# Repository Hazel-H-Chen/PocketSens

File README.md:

# PocketSens Portable Sensor Suite

PocketSens is a portable environmental sensor platform designed to measure environmental and physical data beyond the capabilities of a typical smartphone. The system integrates multiple sensors on a custom four layer PCB and provides real time measurements through a small OLED display and rotary encoder interface.

## Overview

PocketSens is built around an ARM Cortex M0+ SAMD21 microcontroller and communicates with several sensors over an I²C bus. The device collects environmental measurements and displays them directly on the device, allowing users to monitor conditions in real time.

The system is designed as a compact handheld tool capable of measuring atmospheric and environmental parameters in a single portable device. 

## Sensors

The device integrates several sensors including:

* BME680 environmental sensor
  gas, humidity, pressure, temperature
* BMP390 barometric pressure sensor
* MLX90614 infrared temperature sensor
* AS3935 lightning detection sensor

Together these sensors allow the device to measure a wide range of environmental conditions in real time. 

## Hardware

* Custom four layer PCB designed in KiCad
* ARM Cortex M0+ SAMD21 microcontroller
* OLED display for live data output
* Rotary encoder for user interface
* I²C sensor bus architecture

## Features

* Multi sensor environmental monitoring
* Real time data display on OLED screen
* Lightning detection capability
* Infrared temperature sensing
* Compact portable design

## Repository Contents

pcb/
KiCad schematic and PCB layout files

images/
Board photos and layout screenshots

docs/
Additional design notes and documentation

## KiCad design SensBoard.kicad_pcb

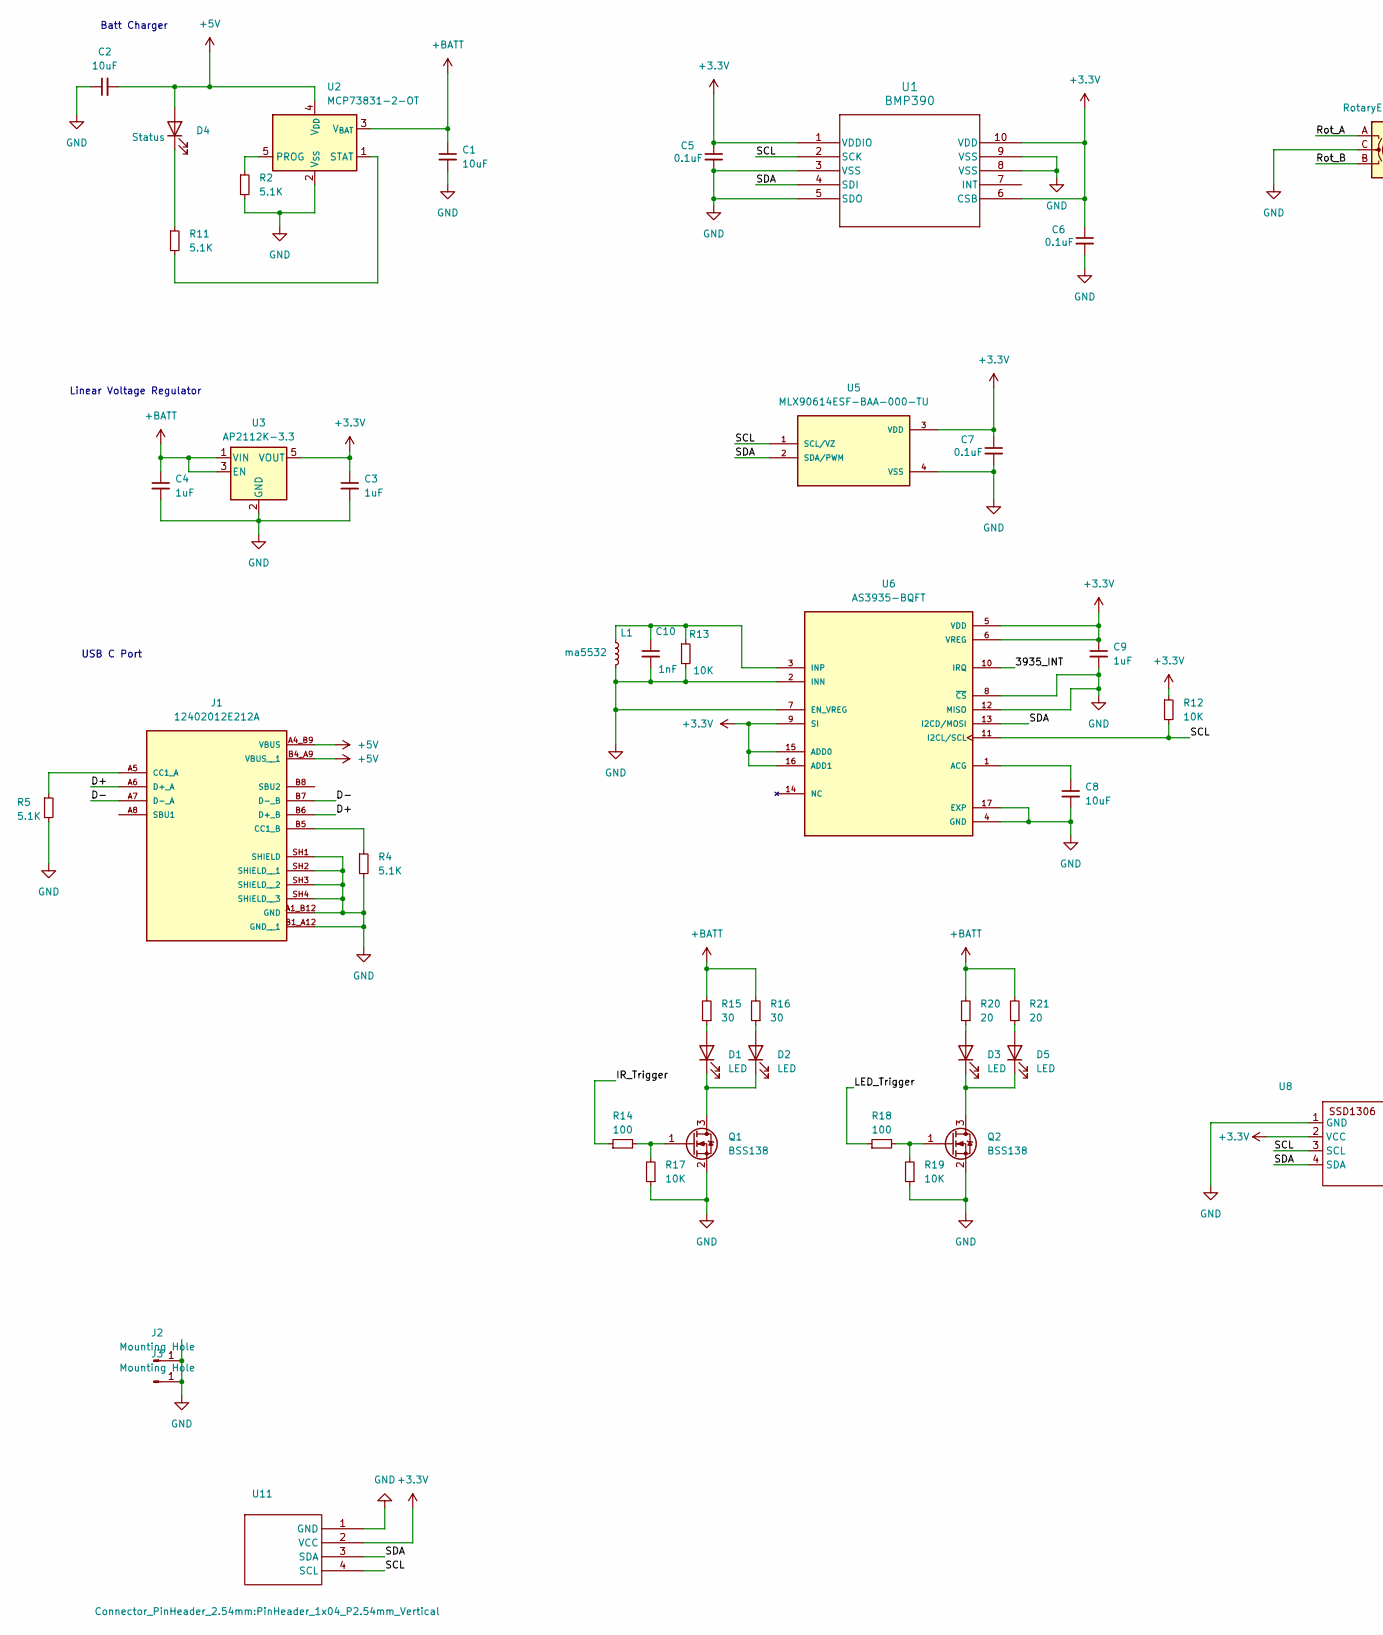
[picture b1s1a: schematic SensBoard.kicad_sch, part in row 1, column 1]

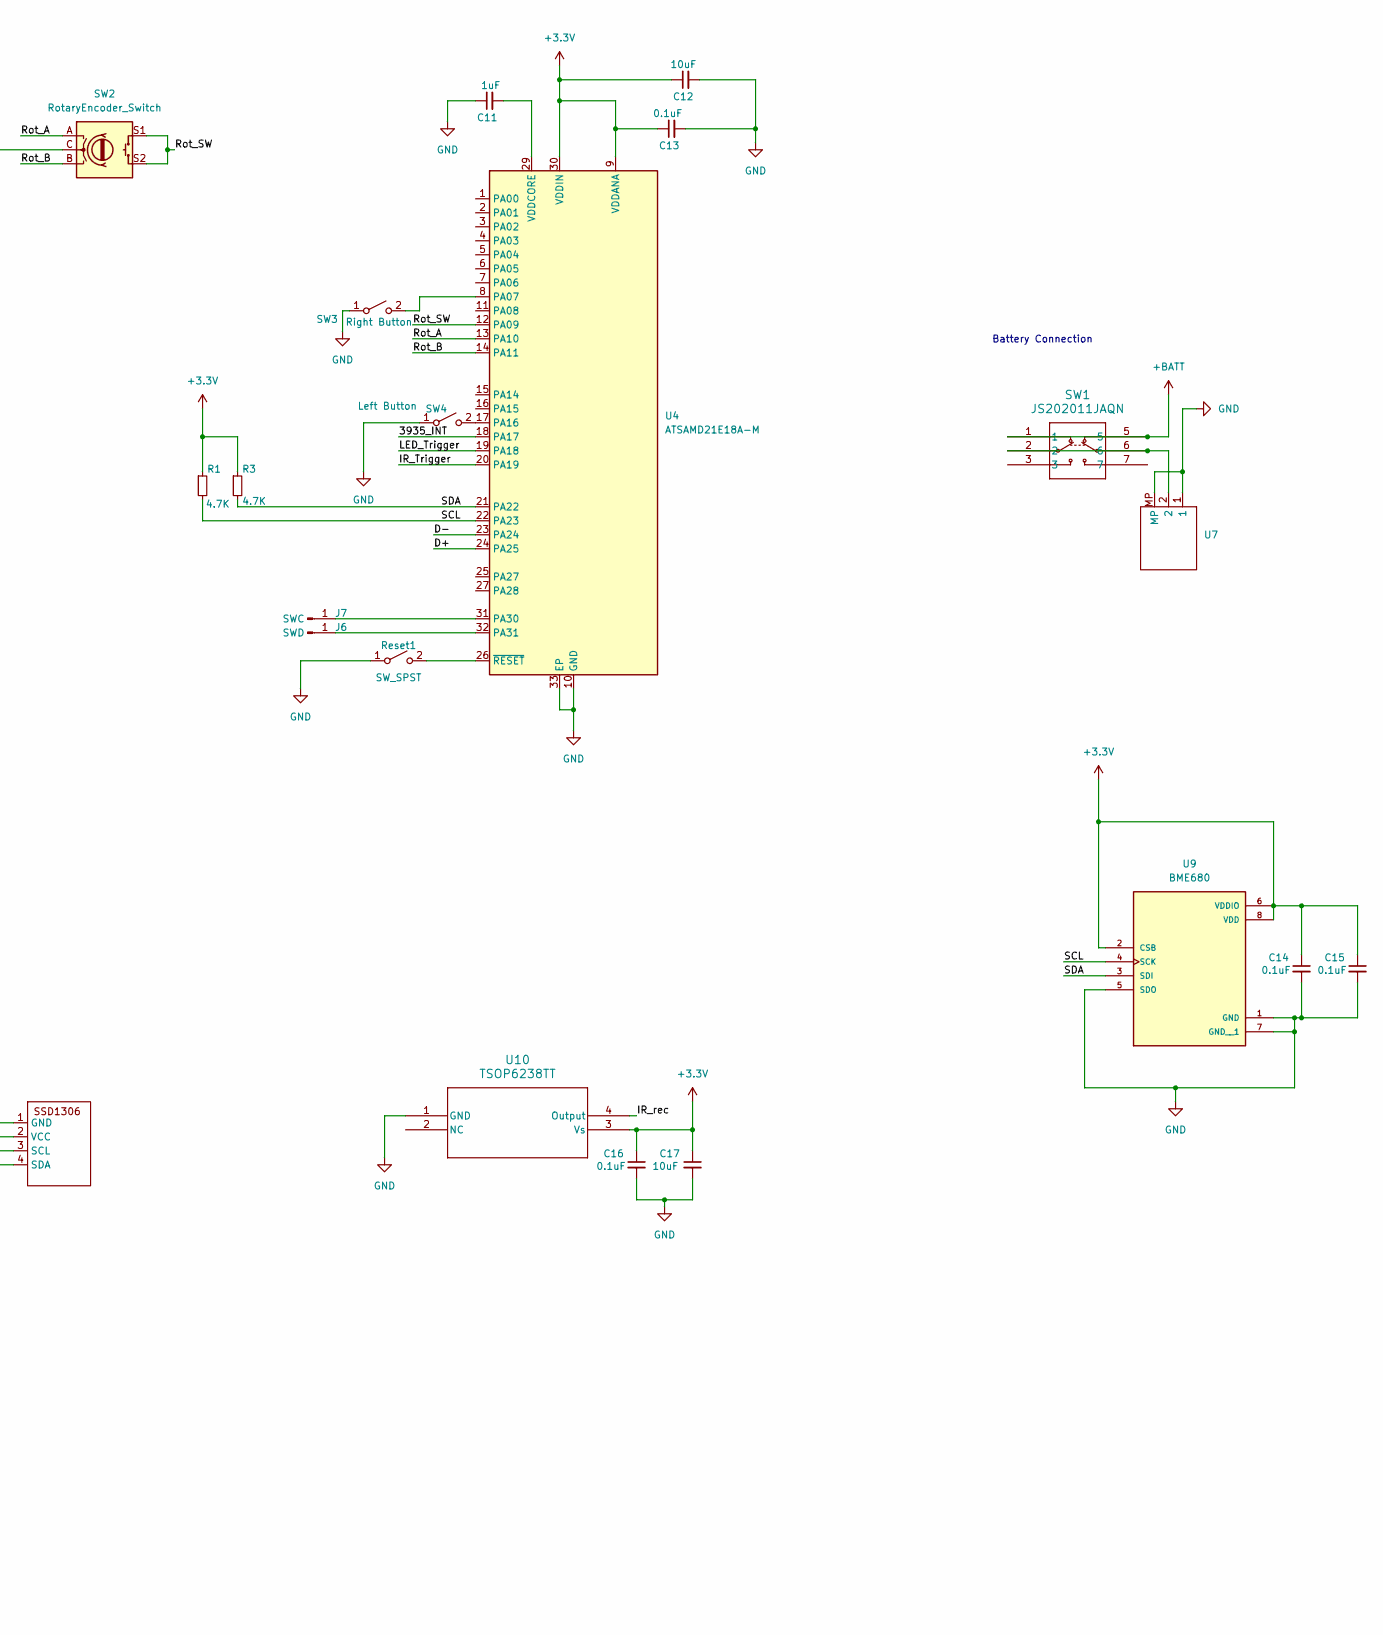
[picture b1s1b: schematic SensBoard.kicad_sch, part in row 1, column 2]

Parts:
C1, C2, C8, C12, C17: 10uF; C_0603_1608Metric
C3, C4, C9, C11: 1uF; C_0603_1608Metric
C5, C6, C7, C13, C14, C15, C16: 0.1uF; C_0603_1608Metric
C10: 1nF; C_0603_1608Metric
D1, D2, D3, D5: LED; LED_PLCC_2835
D4: Status; LED_0603_1608Metric
J1: 12402012E212A; AMPHENOL_12402012E212A; PARTREV 4
J2, J3: Mounting Hole; MountingHole_2.2mm_M2_DIN965_Pad
J6: SWD; PinHeader_1x01_P2.54mm_Vertical
J7: SWC; PinHeader_1x01_P2.54mm_Vertical
L1: ma5532; MA5532-AE
Q1, Q2: BSS138; SOT-23
R1, R3: 4.7K; R_0603_1608Metric
R2, R11: 5.1K; R_0402_1005Metric
R4, R5: 5.1K; R_0603_1608Metric
R12: 10K; R_0402_1005Metric_Pad0.72x0.64mm_HandSolder
R13, R17, R19: 10K; R_0603_1608Metric
R14, R18: 100; R_0603_1608Metric
R15, R16: 30; R_2512_6332Metric
R20, R21: 20; R_0603_1608Metric
Reset1: SW_SPST; SolderJumper-2_P1.3mm_Open_TrianglePad1.0x1.5mm
SW1: JS202011JAQN; JS202011JAQN_CNK
SW2: RotaryEncoder_Switch; RotaryEncoder_Alps_EC11E-Switch_Vertical_H20mm
SW3: Right Button; SW2_KSS341GLFS_CNK
SW4: Left Button; SW2_KSS341GLFS_CNK
U1: BMP390; 10LGA_2X2X0p75_BOS
U2: MCP73831-2-OT; SOT-23-5
U3: AP2112K-3.3; SOT-23-5
U4: ATSAMD21E18A-M; QFN-32-1EP_5x5mm_P0.5mm_EP3.6x3.6mm
U5: MLX90614ESF-BAA-000-TU; TO254P942H425-4; PARTREV 13
U6: AS3935-BQFT; QFN65P400X400X80-17N
U7: JST_PH_S2B-PH-SM4-TB_1x02-1MP_P2.00mm_Horizontal
U8: 128x64OLED
U9: BME680; PSON80P300X300X100-8N; PARTREV 1.9
U10: TSOP6238TT; SOJ_6238TT_VIS-M
U11: PinHeader_1x04_P2.54mm_Vertical

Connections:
+3.3V: C3.1, C5.1, C6.1, C7.1, C9.1, C12.1, C13.1, C14.1, C15.1, C16.1, C17.1, R1.1, R3.1, R12.1, U1.1 (VDDIO), U1.6 (CSB), U1.10 (VDD), U3.5 (VOUT), U4.9 (VDDANA), U4.30 (VDDIN), U5.3 (VDD), U6.5 (VDD), U6.6 (VREG), U6.9 (SI), U6.15 (ADD0), U6.16 (ADD1), U8.2 (VCC), U9.2 (CSB), U9.6 (VDDIO), U9.8 (VDD), U10.3 (Vs), U11.2 (VCC)
+5V: C2.2, D4.2 (A), J1.A4_B9 (VBUS), J1.B4_A9 (VBUS__1), U2.4 (V_{DD})
+BATT: C1.1, C4.1, R15.2, R16.2, R20.2, R21.2, SW1.1, SW1.5, U2.3 (V_{BAT}), U3.1 (VIN), U3.3 (EN)
/3935_INT: U4.18 (PA17), U6.10 (IRQ)
/D+: J1.A6 (D+_A), J1.B6 (D+_B), U4.24 (PA25)
/D-: J1.A7 (D-_A), J1.B7 (D-_B), U4.23 (PA24)
/IR_Trigger: R14.1, U4.20 (PA19)
/IR_rec: U10.4 (Output)
/LED_Trigger: R18.1, U4.19 (PA18)
/Rot_A: SW2.A, U4.13 (PA10)
/Rot_B: SW2.B, U4.14 (PA11)
/Rot_SW: SW2.S1, SW2.S2, U4.12 (PA09)
/SCL: R1.2, R12.2, U1.2 (SCK), U4.22 (PA23), U5.1 (SCL/VZ), U6.11 (I2CL/SCL), U8.3 (SCL), U9.4 (SCK), U11.4 (SCL)
/SDA: R3.2, U1.4 (SDI), U4.21 (PA22), U5.2 (SDA/PWM), U6.13 (I2CD/MOSI), U8.4 (SDA), U9.3 (SDI), U11.3 (SDA)
GND: C1.2, C2.1, C3.2, C4.2, C5.2, C6.2, C7.2, C8.2, C9.2, C10.2, C11.1, C12.2, C13.2, C14.2, C15.2, C16.2, C17.2, J1.A1_B12 (GND), J1.B1_A12 (GND__1), J1.SH1 (SHIELD), J1.SH2 (SHIELD__1), J1.SH3 (SHIELD__2), J1.SH4 (SHIELD__3), J2.1, J3.1, L1.2, Q1.2 (S), Q2.2 (S), R2.2, R4.2, R5.2, R13.2, R17.1, R19.1, Reset1.1 (A), SW2.C, SW3.1 (A), SW4.1 (A), U1.3 (VSS), U1.5 (SDO), U1.8 (VSS), U1.9 (VSS), U2.2 (V_{SS}), U3.2 (GND), U4.10 (GND), U4.28 (GND), U4.33 (EP), U5.4 (VSS), U6.2 (INN), U6.4 (GND), U6.7 (EN_VREG), U6.8 (~CS), U6.12 (MISO), U6.17 (EXP), U7.1, U7.MP, U8.1 (GND), U9.1 (GND), U9.5 (SDO), U9.7 (GND__1), U10.1 (GND), U11.1 (GND)
unnamed: D1.2 (A), R15.1
unnamed: D1.1 (K), D2.1 (K), Q1.3 (D)
unnamed: D2.2 (A), R16.1
unnamed: D3.2 (A), R20.1
unnamed: D3.1 (K), D5.1 (K), Q2.3 (D)
unnamed: D4.1 (K), R11.1
unnamed: D5.2 (A), R21.1
unnamed: J1.A5 (CC1_A), R5.1
unnamed: J1.B5 (CC1_B), R4.1
unnamed: J6.1, U4.32 (PA31)
unnamed: J7.1, U4.31 (PA30)
unnamed: Q1.1 (G), R14.2, R17.2
unnamed: Q2.1 (G), R18.2, R19.2
unnamed: Reset1.2 (B), U4.26 (~RESET)
unnamed: SW1.2, SW1.6, U7.2
unnamed: SW3.2 (B), U4.8 (PA07)
unnamed: SW4.2 (B), U4.17 (PA16)
unnamed: R2.1, U2.5 (PROG)
unnamed: R11.2, U2.1 (STAT)
unnamed: C11.2, U4.29 (VDDCORE)
unnamed: C8.1, U6.1 (ACG)
unnamed: C10.1, L1.1, R13.1, U6.3 (INP)

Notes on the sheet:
Batt Charger
Linear Voltage Regulator
USB C Port
Battery Connection

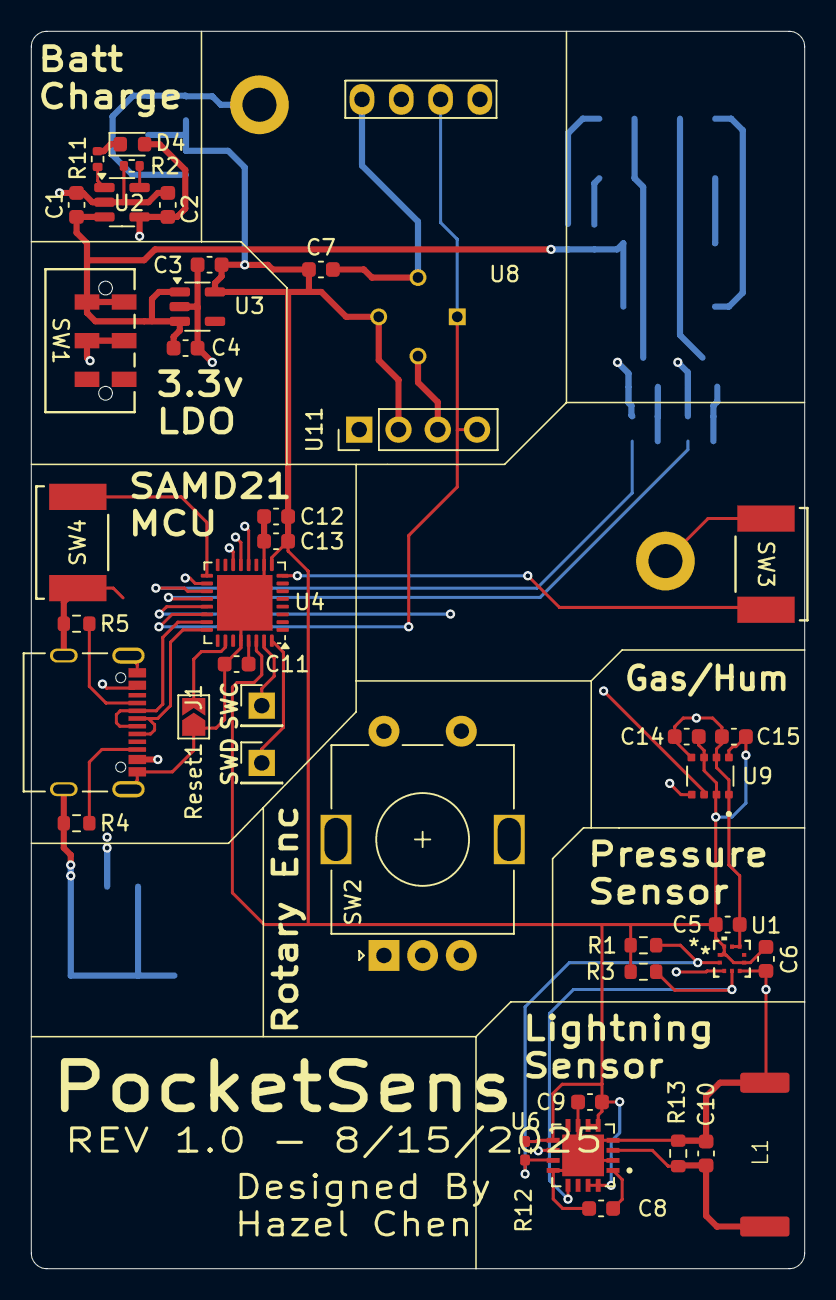
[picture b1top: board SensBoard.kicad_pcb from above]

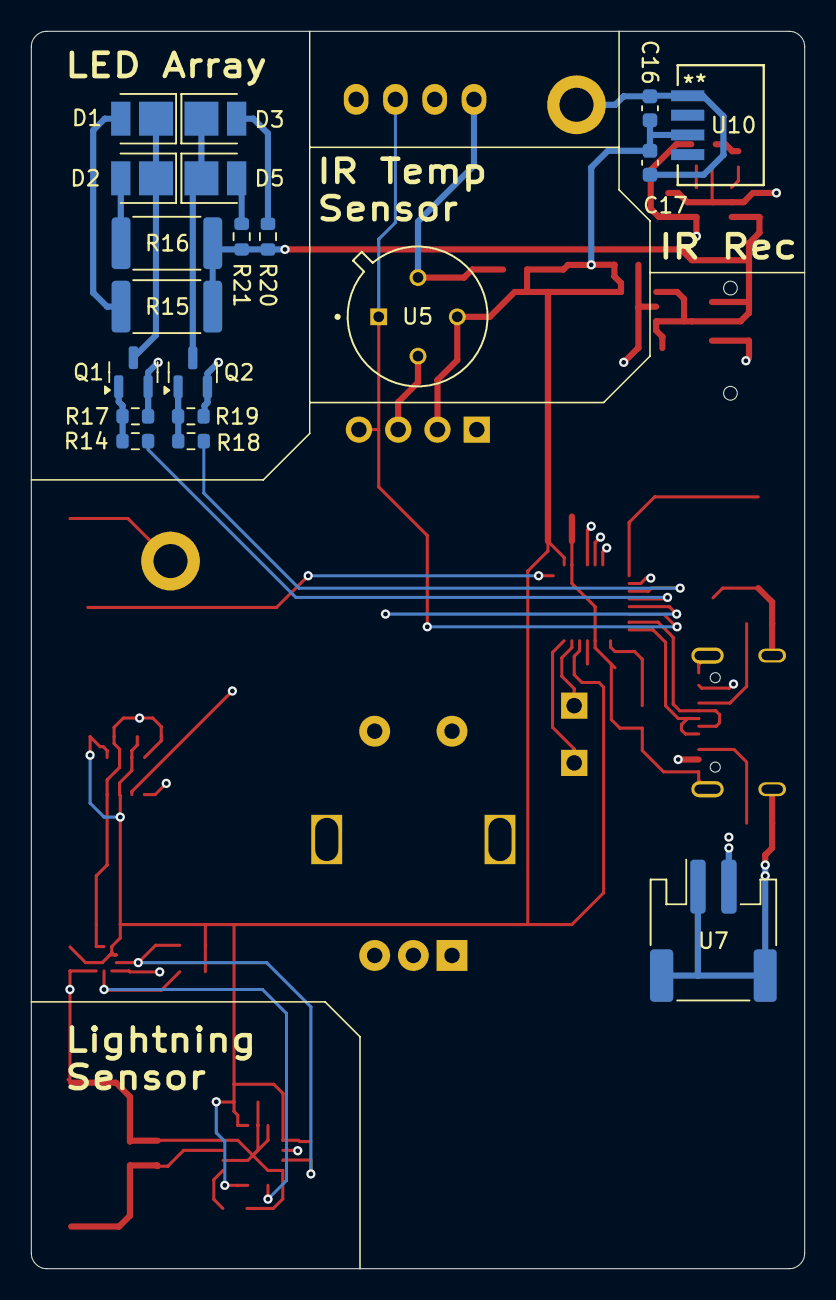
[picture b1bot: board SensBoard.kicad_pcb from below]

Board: 4 copper layers, 50.0 x 80.0 mm, 62 parts (19 on the bottom side), 36 nets.

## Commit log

2026-03-18 Rename SensBoard.kicad_pcb to pcb/SensBoard.kicad_pcb
2026-03-18 Rename SensBoard.kicad_pro to pcb/SensBoard.kicad_pro
2026-03-18 Rename SensBoard.kicad_sch to pcb/SensBoard.kicad_sch
